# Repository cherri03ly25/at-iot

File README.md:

# BLE Sensor Board and Web Interface

This project defines a sensor board that broadcasts information to an IoT gateway, which then pushes the data to Azure IoT Hub. The data is then transferred to a node.js webserver that then broadcasts it to browser clients.

## Contents

* KiCAD schematics and PCB design for an nRF52840-powered sensor board
* source code for the nRF52840, required for it to send data to an IoT gateway utilizing BLE beacons
* source code for a node.js webserver capable of receiving data from Azure IoT Hub and broadcasting it to the users of a website
* the documentation for all of the above, instructions

## Installation Instructions

All parts of this project (webserver, firmware and KiCAD schematics) come with installation instructions. They can be found in their respective directories, in the INSTALL file.

## Licensing

See LICENSE.

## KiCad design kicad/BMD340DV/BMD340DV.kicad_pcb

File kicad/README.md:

# README

## Prerequisites

To view or edit pcb design files you need to use KiCad v5.0 program. 

Required libraries you can get from SnapEDA: https://www.snapeda.com/

Needed parts:

* Rigado BMD-340
* LP5907MFX-3.3_NOPB
* BMI055
* APDS-9960 

## Installing KiCAD
 
You can get KiCad for your operating system from http://kicad-pcb.org/ website.

1. Install KiCAD
2. Run KiCAD
3. Use recommended library settings
4. Get project from GitHub
5. Open .pro file from project folder with KiCAD
6. Now you can modify schema/layout with eeschema/pcbnew
7. To import symbol libraries go in Eeschema to "Preferences->Manage Symbol Libraries" and add.
8. To import footprint libraries go in Pcbnew to "Preferences->Manage Footprint Libraries" and add.

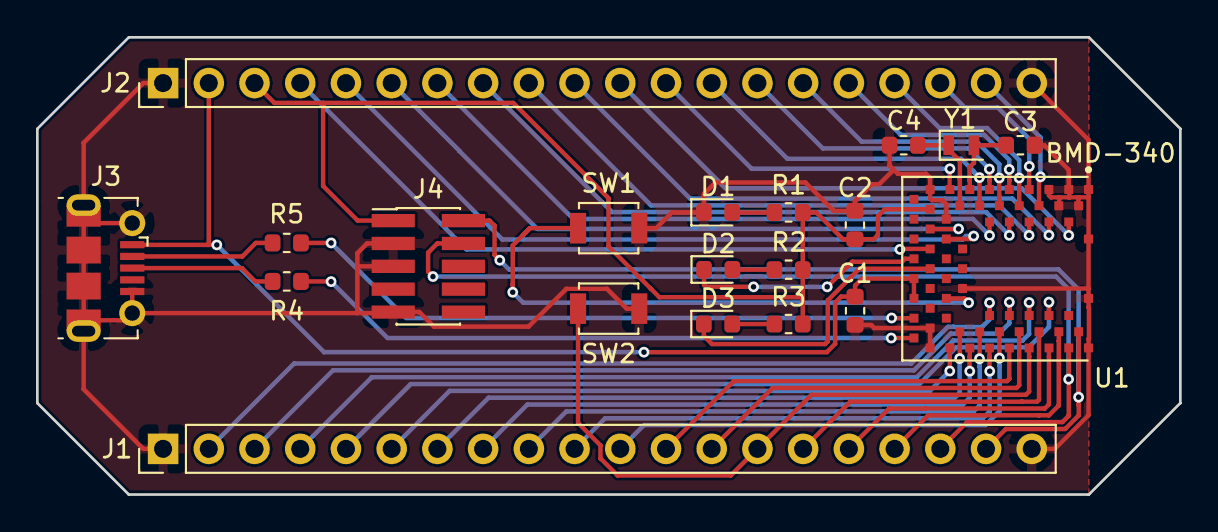
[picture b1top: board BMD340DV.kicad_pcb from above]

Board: 2 copper layers, 63.5 x 25.4 mm, 20 parts (0 on the bottom side), 49 nets.

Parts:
C1: 4,7uF; C_0603_1608Metric
C2: 4.7uF; C_0603_1608Metric
C3, C4: 9pF; C_0603_1608Metric
D1, D2, D3: LED; LED_0603_1608Metric
J1, J2: Conn_01x20; PinHeader_1x20_P2.54mm_Vertical
J3: USB_B_Micro; USB_Micro-B_Molex-105017-0001
J4: Conn_02x05_Odd_Even; PinHeader_2x05_P1.27mm_Vertical_SMD
R1, R2, R3: 1k; R_0603_1608Metric
R4, R5: 27; R_0603_1608Metric
SW1, SW2: SW_Push; SW_SPST_B3U-1000P
U1: BMD-340; RIGADO_BMD-340-A-R
Y1: Crystal; Crystal_SMD_TXC_9HT11-2Pin_2.0x1.2mm

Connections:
/+: J3.3, R4.2
/-: J3.2, R5.2
/BUTTON1: SW1.1, U1.26
/D+: R4.1, U1.68
/D-: R5.1, U1.67
/LED1: D2.1, U1.64
/LED2: D3.1, U1.23
/P0.02: J2.12, U1.15
/P0.03: J2.6, U1.19
/P0.04: J2.5, U1.20
/P0.05: J2.4, U1.21
/P0.13: J1.6, U1.31
/P0.14: J1.7, U1.32
/P0.15: J1.8, U1.33
/P0.16: J1.9, U1.34
/P0.17: J1.10, U1.35
/P0.19: J1.12, U1.37
/P0.20: J1.13, U1.38
/P0.21: J1.11, U1.36
/P0.22: J1.15, U1.40
/P0.23: J1.16, U1.41
/P0.24: J1.17, U1.42
/P0.25: J2.19, U1.6
/P0.26: J2.18, U1.7
/P0.27: J2.17, U1.8
/P0.28: J2.16, U1.9
/P0.29: J2.15, U1.10
/P0.30: J2.14, U1.11
/P0.31: J2.13, U1.12
/P1.00: J1.2, U1.56
/P1.01: J1.3, U1.57
/P1.02: J1.4, U1.58
/P1.03: J1.5, U1.59
/P1.05: J2.11, U1.48
/P1.06: J2.10, U1.49
/P1.07: J2.9, U1.50
/P1.08: J2.8, U1.51
/P1.09: J2.7, U1.52
/RST: J1.14, SW2.2, U1.39
/SWCLK: J1.18, J4.4, U1.43
/SWDIO: J1.19, J4.2, U1.44
/VBUS: C1.2, J2.2, J3.1, U1.65, U1.66
/VCC: C2.1, J2.3, J4.1, R1.1, R2.1, R3.1, U1.17
GNDREF: C1.1, C2.2, C3.2, C4.2, D1.1, J1.1, J1.20, J2.1, J2.20, J3.5, J3.6, J4.3, J4.5, J4.9, SW1.2, SW2.1, U1.1, U1.2, U1.3, U1.4, U1.5, U1.16, U1.18, U1.29, U1.30, U1.45, U1.46, U1.47, U1.55
unnamed: C3.1, U1.13, Y1.2
unnamed: C4.1, U1.14, Y1.1
unnamed: D1.2, R1.2
unnamed: D2.2, R2.2
unnamed: D3.2, R3.2

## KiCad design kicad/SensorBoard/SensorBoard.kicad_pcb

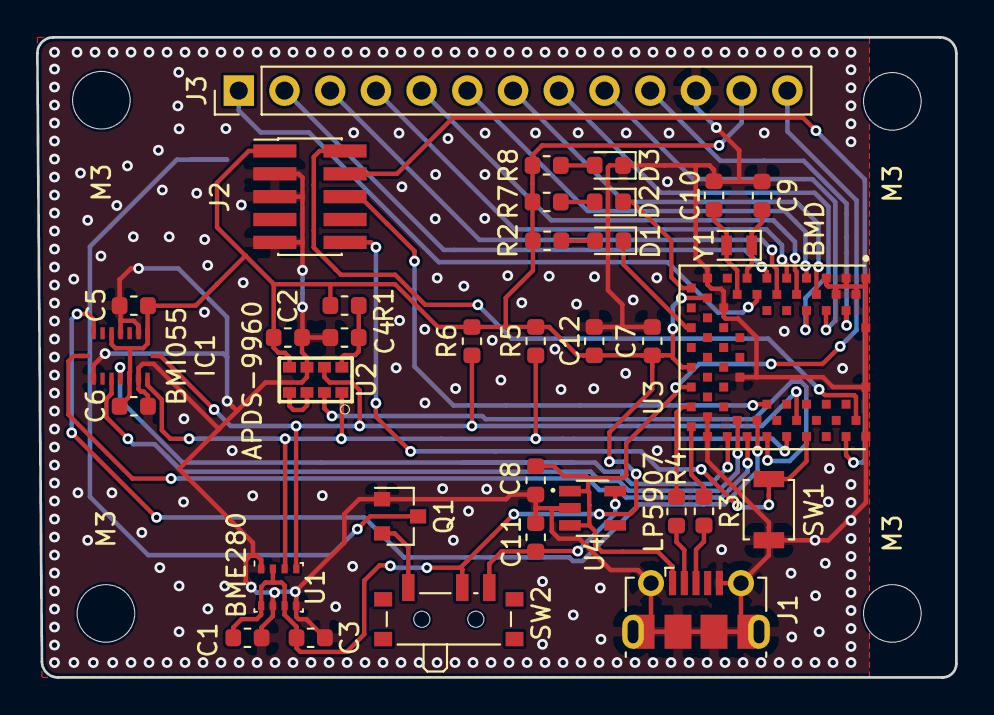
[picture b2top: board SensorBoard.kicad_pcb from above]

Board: 2 copper layers, 51.1 x 35.6 mm, 40 parts (1 on the bottom side), 40 nets.

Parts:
BT1: Battery_Cell; BatteryHolder_Keystone_3034_1x20mm
C1, C2, C3, C4, C5, C6, C12: 100nF; C_0603_1608Metric
C7, C8: 4,7uF; C_0603_1608Metric
C9, C10: 12,5pF; C_0603_1608Metric
C11: 10uF; C_0603_1608Metric
D1, D2: LED; LED_0603_1608Metric
D3: LED POWER; LED_0603_1608Metric
IC1: BMI055; QFN50P300X450X100-16N
J1: USB_B_Micro; USB_Micro-B_Molex-105017-0001
J2: Conn_02x05_Odd_Even; PinHeader_2x05_P1.27mm_Vertical_SMD
J3: Conn_01x13; PinHeader_1x13_P2.54mm_Vertical
M3, M3#2, M3#3, M3#4: MountingHole_3.2mm_M3
Q1: TP0610T; SOT-23
R1: 22; R_0603_1608Metric
R2, R7, R8: 1k; R_0603_1608Metric
R3, R4: 27; R_0603_1608Metric
R5, R6: 4,7k; R_0603_1608Metric
SW1: SW_Push; SW_SPST_B3U-1000P
SW2: SW_SPDT; SW_SPDT_PCM12
U1: BME280; Bosch_LGA-8_2.5x2.5mm_P0.65mm_ClockwisePinNumbering
U2: APDS-9960
U3: BMD; RIGADO_BMD-340-A-R
U4: LP5907; SOT95P280X145-5N
Y1: 32.768KHz; Crystal_SMD_TXC_9HT11-2Pin_2.0x1.2mm

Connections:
/+: J1.3, R3.2
/-: J1.2, R4.2
/D+: R3.1, U3.68
/D-: R4.1, U3.67
/INT1A: IC1.16, U3.33
/INT1G: IC1.12, U3.31
/INT2A: IC1.1, U3.34
/INT2G: IC1.13, U3.32
/INTL: U2.2, U3.35
/LED1: D1.1, U3.63
/LED2: D2.1, U3.61
/P0.25: J3.7, U3.6
/P0.26: J3.6, U3.7
/P0.27: J3.5, U3.8
/P0.28: J3.4, U3.9
/P0.29: J3.3, U3.10
/P0.30: J3.2, U3.11
/P0.31: J3.1, U3.12
/P1.05: J3.10, U3.48
/P1.06: J3.9, U3.49
/P1.07: J3.8, U3.50
/RST: J2.10, SW1.1, U3.39
/SCL: IC1.8, R6.2, U1.4, U2.7, U3.38
/SDA: IC1.9, R5.2, U1.3, U2.1, U3.37
/SWCLK: J2.4, U3.43
/SWDIO: J2.2, U3.44
/SWO: J2.6, U3.56
/VBUS: C8.1, J1.1, J3.13, U3.66, U4.1, U4.3
/VCC: C1.1, C2.1, C3.1, C5.1, C6.1, C7.2, C12.1, IC1.3, IC1.7, IC1.11, J2.1, J3.12, R1.2, R2.1, R5.1, R6.1, R7.1, R8.1, SW2.2, U1.2, U1.6, U1.8, U2.5, U3.17, U3.65
/VCCB: Q1.2, SW2.1
/VCCR: C11.1, SW2.3, U4.5
/XTAL1: C9.2, U3.13, Y1.1
/XTAL2: C10.2, U3.14, Y1.2
GNDREF: BT1.2, C1.2, C2.2, C3.2, C4.2, C5.2, C6.2, C7.1, C8.2, C9.1, C10.1, C11.2, C12.2, D3.1, IC1.4, IC1.6, IC1.10, IC1.15, J1.5, J1.6, J2.3, J2.5, J2.9, J3.11, Q1.1, SW1.2, U1.1, U1.5, U1.7, U2.6, U3.1, U3.2, U3.3, U3.4, U3.5, U3.16, U3.18, U3.29, U3.30, U3.45, U3.46, U3.47, U3.55, U4.2
unnamed: BT1.1, Q1.3
unnamed: C4.1, R1.1, U2.8
unnamed: D1.2, R2.2
unnamed: D2.2, R7.2
unnamed: D3.2, R8.2
unnamed: U2.3, U2.4

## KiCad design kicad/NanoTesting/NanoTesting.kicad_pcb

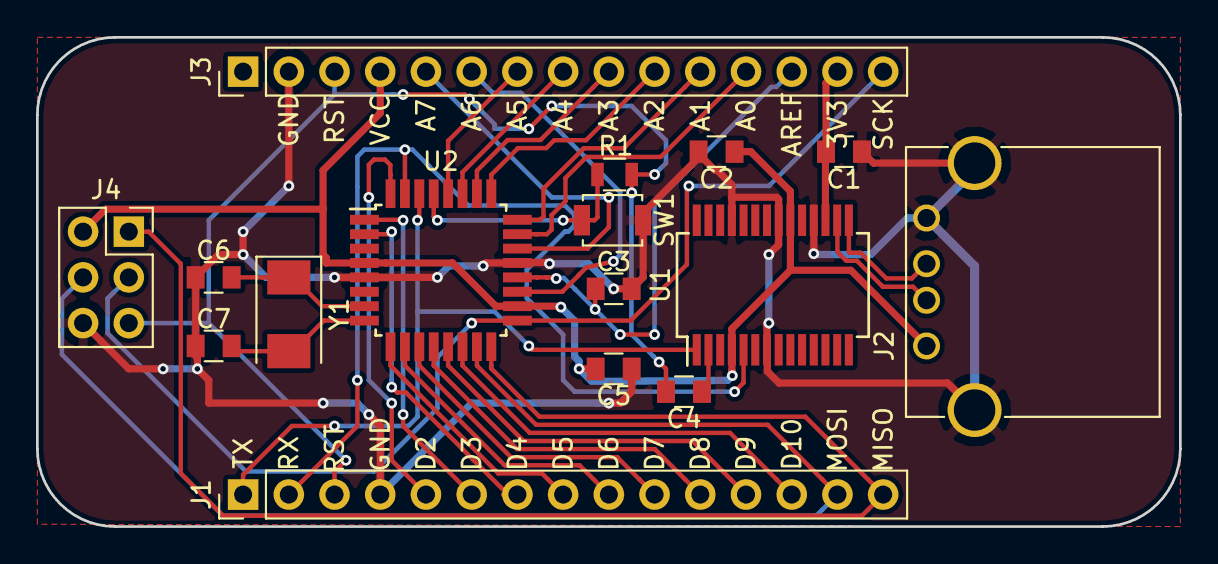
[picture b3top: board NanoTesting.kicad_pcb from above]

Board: 2 copper layers, 63.5 x 27.2 mm, 16 parts (0 on the bottom side), 33 nets.

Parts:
C1, C2, C3, C4, C5: 100nF; C_0805
C6, C7: 18pF; C_0805
J1, J3: Conn_01x15; Socket_Strip_Straight_1x15_Pitch2.54mm
J2: USB_A
J4: Conn_02x03_Odd_Even; Socket_Strip_Straight_2x03_Pitch2.54mm
R1: 1K; R_0805
SW1: SW_Push; SW_SPST_B3U-1000P
U1: FT232RL; SSOP-28_5.3x10.2mm_Pitch0.65mm
U2: ATMEGA328PB-AU; TQFP-32_7x7mm_Pitch0.8mm
Y1: 16MHz; Crystal_SMD_Abracon_ABM3-2pin_5.0x3.2mm

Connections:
/3V3: C1.1, J3.14, U1.17
/A0: J3.12, U2.23
/A1: J3.11, U2.24
/A2: J3.10, U2.25
/A3: J3.9, U2.26
/A4: J3.8, U2.27
/A5: J3.7, U2.28
/A6: J3.6, U2.19
/A7: J3.5, U2.22
/AREF: C3.1, J3.13, U2.20
/D2: J1.5, U2.32
/D3: J1.6, U2.1
/D4: J1.7, U2.2
/D5: J1.8, U2.9
/D6: J1.9, U2.10
/D7: J1.10, U2.11
/D8: J1.11, U2.12
/D9: J1.12, U2.13
/D10: J1.13, U2.14
/DTR: C4.1, U1.2
/MISO: J1.15, J4.1, U2.16
/MOSI: J1.14, J4.4, U2.15
/RST: C4.2, J1.3, J3.3, J4.5, R1.1
/RX: J1.2, U1.5, U2.31
/SCK: J3.15, J4.3, U2.17
/TX: J1.1, U1.1, U2.30
/VCC: C2.2, C5.2, J2.1, J3.4, J4.2, U1.4, U1.20, U2.4, U2.18
/XTAL1: C6.2, U2.7, Y1.1
/XTAL2: C7.2, U2.8, Y1.2
GND: C1.2, C2.1, C3.2, C5.1, C6.1, C7.1, J1.4, J2.4, J2.5, J3.2, J4.6, SW1.2, U1.7, U1.18, U1.21, U1.25, U2.5, U2.21
unnamed: J2.2, U1.16
unnamed: J2.3, U1.15
unnamed: R1.2, SW1.1, U2.29

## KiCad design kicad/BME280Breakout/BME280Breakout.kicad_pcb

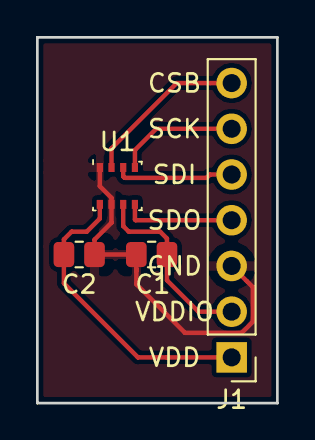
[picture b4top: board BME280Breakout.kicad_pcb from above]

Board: 2 copper layers, 13.3 x 20.3 mm, 4 parts (0 on the bottom side), 7 nets.

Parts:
C1, C2: 100nF; C_0805_2012Metric
J1: Conn_01x07; PinHeader_1x07_P2.54mm_Vertical
U1: BME280; Bosch_LGA-8_2.5x2.5mm_P0.65mm_ClockwisePinNumbering

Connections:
/CSB: J1.7, U1.2
/SCK: J1.6, U1.4
/SDI: J1.5, U1.3
/SDO: J1.4, U1.5
/VDD: C2.2, J1.1, U1.8
/VDDIO: C1.2, J1.2, U1.6
GND: C1.1, C2.1, J1.3, U1.1, U1.7

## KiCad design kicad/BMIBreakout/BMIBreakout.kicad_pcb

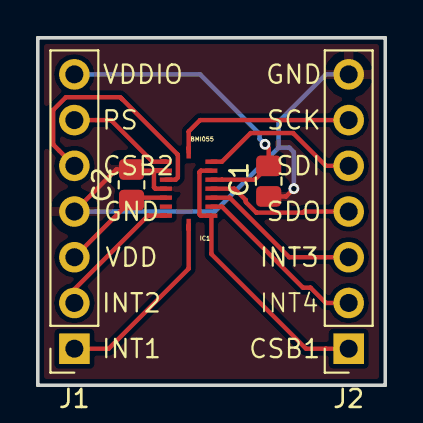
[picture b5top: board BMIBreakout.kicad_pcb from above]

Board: 2 copper layers, 19.3 x 19.3 mm, 5 parts (0 on the bottom side), 13 nets.

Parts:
C1, C2: C; C_0805_2012Metric
IC1: BMI055; QFN50P300X450X100-16N
J1, J2: Conn_01x07; PinSocket_1x07_P2.54mm_Vertical

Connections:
/CSB1: IC1.14, J2.2
/CSB2: IC1.5, J1.5
/INT1: IC1.16, J1.1
/INT2: IC1.1, J1.2
/INT3: IC1.12, J2.4
/INT4: IC1.13, J2.3
/PS: IC1.7, J1.6
/SCK: IC1.8, J2.6
/SDI: IC1.9, J2.5
/SDO: IC1.10, IC1.15, J2.1
/VDD: C2.1, IC1.3, J1.3
/VDDIO: C1.1, IC1.11, J1.7
GND: C1.2, C2.2, IC1.4, IC1.6, J1.4, J2.7

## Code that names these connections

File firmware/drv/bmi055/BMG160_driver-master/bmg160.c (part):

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 *	v_pwu_ext_tri_select_u8	 |	Trigger source
 * --------------------------|-------------------------
 *      0x00                 |      No
 *		0x01                 |   INT1 pin
 *		0x02                 |   INT2 pin
 *		0x03                 |  SDO pin(SPI3 mode)
 *
 *
 *	@return results of bus communication function
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 *	v_pwu_ext_tri_select_u8	 |	Trigger source
 * --------------------------|-------------------------
 *      0x00                 |      No
 *		0x01                 |   INT1 pin
 *		0x02                 |   INT2 pin
 *		0x03                 |  SDO pin(SPI3 mode)
 *
 *
 *	@return results of bus communication function
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
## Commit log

2018-08-31 Project submission.
2018-09-02 Post-submission polish, commentary and bugfixes
2018-09-02 More bugfixes and polish. Migrating client to OOP half-way done.
2018-09-02 Small fix to simulated device. Example device config added.
2018-09-03 Removed redundant webpage files
2018-09-03 Created Pages.
2018-09-03 Fill in the rest of the files...
2018-09-03 Redoing the Pages...
2018-09-03 Revert "Redoing the Pages..."
    This reverts commit a2eb108ebbc1100583ee8380bc15e0ca4004b2e9.

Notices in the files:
firmware/drv/bmi055/BMG160_driver-master/bmg160.c:
Copyright (C) 2010 - 2015 Bosch Sensortec GmbH
License:
Redistribution and use in source and binary forms, with or without
